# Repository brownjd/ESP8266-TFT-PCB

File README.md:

# ESP8266-TFT-PCB
## Eagle files for a printed circuit board to connect a Node MCU ESP8266 Wifi board and a 1.8 TFT ST7735 display.

Below are the pin mappings from the display to the board. 

| TFT     | ESP    |
|:-------:|:------:|
| SCL/SCK |  D5    |
| SDA/MOSI|  D7    |
| VCC     | +3.3V  |
| LED-    | GND    |
| LED+    | VIN +5V|
| GND     | GND    |

## Here's what the board looks like:

### Top

### Bottom

Here are the traces.

### Top Layer

### Bottom Layer

## Here's [what you can do with it](https://github.com/brownjd/ESPStockTicker)

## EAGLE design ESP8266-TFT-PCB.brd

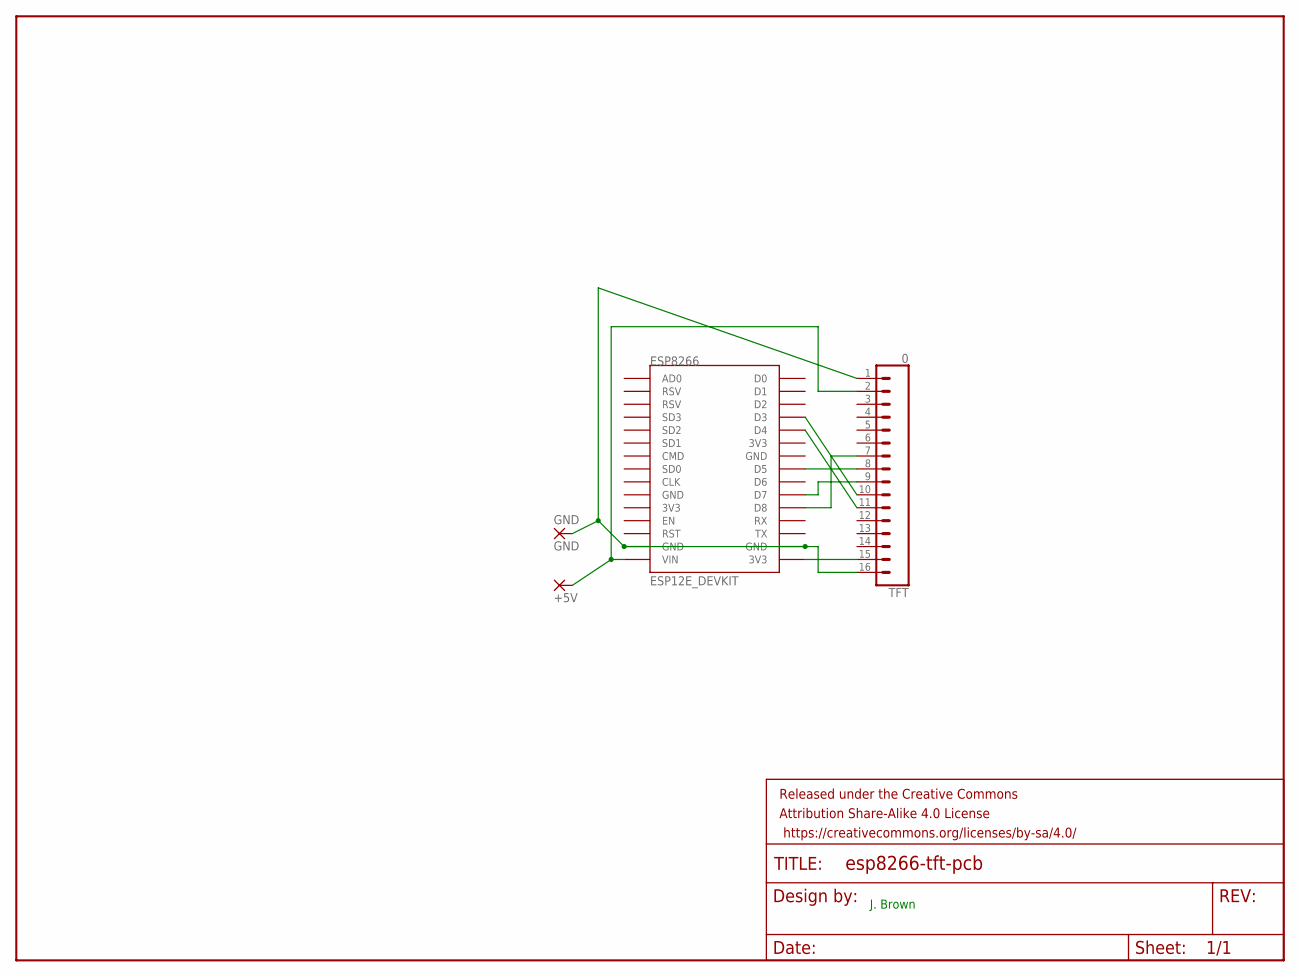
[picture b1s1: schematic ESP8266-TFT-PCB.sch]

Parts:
ESP8266: ESP12E_DEVKIT
FRAME1: FRAME-LETTER; CREATIVE_COMMONS
GND: GND; 3,81/1,4
TFT: 0; 1X16
VCC: +5V; 3,81/1,4

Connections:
GND: ESP8266.GND@1 (GND), ESP8266.GND@3 (GND), GND.1, TFT.1, TFT.16
unnamed: ESP8266.3V3@2 (3V3), TFT.15
unnamed: ESP8266.D8, TFT.7
unnamed: ESP8266.D5, TFT.8
unnamed: ESP8266.D7, TFT.9
unnamed: ESP8266.D4, TFT.11
unnamed: ESP8266.D3, TFT.10
VCC: ESP8266.VIN, TFT.2, VCC.1

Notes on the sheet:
J. Brown

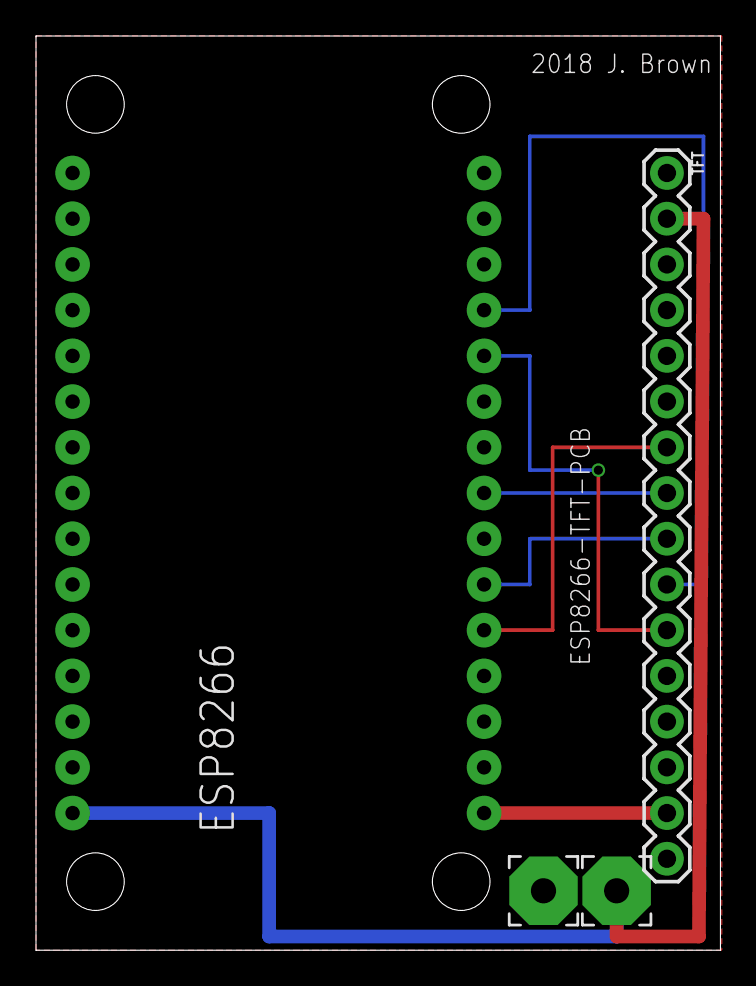
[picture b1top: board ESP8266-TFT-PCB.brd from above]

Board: 2 copper layers, 38.0 x 50.8 mm, 5 parts (0 on the bottom side), 8 nets.

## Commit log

2018-05-11 Amend Author
2018-05-11 Updated readme.
2018-05-11 Fix readme.
2018-05-11 table
2018-05-11 license
2018-05-30 Renamed and moved power connectors
2018-05-30 Cleanup
2018-05-30 Rename files
2018-05-30 Updated images.

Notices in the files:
parts and their libraries:
SparkFun-Connectors: Licensing: Creative Commons ShareAlike 4.0 International - https://creativecommons.org/licenses/by-sa/4.0
SparkFun-Aesthetics: Released under the Creative Commons Attribution Share-Alike 4.0 License
SparkFun-Aesthetics: https://creativecommons.org/licenses/by-sa/4.0
